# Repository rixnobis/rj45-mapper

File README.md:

# rj45-mapper

A bench probe for unknown cables that have an 8P8C (RJ45) plug on one end and loose
wires on the other. Plug the cable into the jack and touch one loose wire to the
pad. The LED for the jack pin that wire lands on lights up. If two pins are shorted
together in the cable, two LEDs light.

## How it works

The pad sits at 5 V through 1k. Each jack pin drives one input of a ULN2803A, and
each ULN output sinks one red LED through 330R (about 7 mA). A wire grounded at its
far end draws 5 mA from the pad, so it is not a short. A finger across the pad and a
wire (around 1 Mohm) puts the input under 0.1 V, far below the two-VBE turn-on of the
ULN input, so only metal contact lights an LED. Power is USB-C at 5 V, with a
separate 5.1k on each CC pin.

## Parts

JLC assembles everything except the jack: `fab/rj45-mapper-bom.csv` and
`fab/rj45-mapper-cpl.csv`. The jack is any unshielded right-angle 8P8C on the TE
5555164 / Amphenol 54602 land pattern (8 x 0.89 mm on 1.27 mm pitch, rows 2.54 mm
apart, 3.25 mm pegs 11.43 mm apart), bought separately and hand-soldered; see
`fab/hand-solder.csv`. Its plug face sits flush with the board edge. The 3D model
is TE 5555164-1. Check the part rotations in JLC's placement preview before
ordering (U1 and the LEDs are polarized).

## Case

`case/case.scad` (OpenSCAD) has a base and a lid that clamp the board between them
with four M3x18 screws through the mounting holes. The pilot holes in the base are
2.6 mm for self-tapping screws; set `PILOT_D = 4.0` for heat-set inserts. The lid has
one light tube per LED, with the channel numbers debossed beside them, and openings
for the jack, the USB-C plug and the pad. There are no overhangs that need support.
`case/fit_check.py` tests every component triangle of the populated board against
the case solids (the board meshes are not closed, so OpenSCAD cannot intersect them),
and casts rays along the plug path from outside the case to check that a plug can
reach 3 mm into the jack.

## Building

`tools/build.sh` regenerates everything: schematic, ERC, a pin-by-pin netlist check,
placement and a scripted route, pours, DRC with schematic parity, a routing geometry
check, renders and fab outputs. `case/render.sh` makes the case STLs and renders.
Needs KiCad 10 with `kicad-packages3d`, OpenSCAD and ImageMagick.

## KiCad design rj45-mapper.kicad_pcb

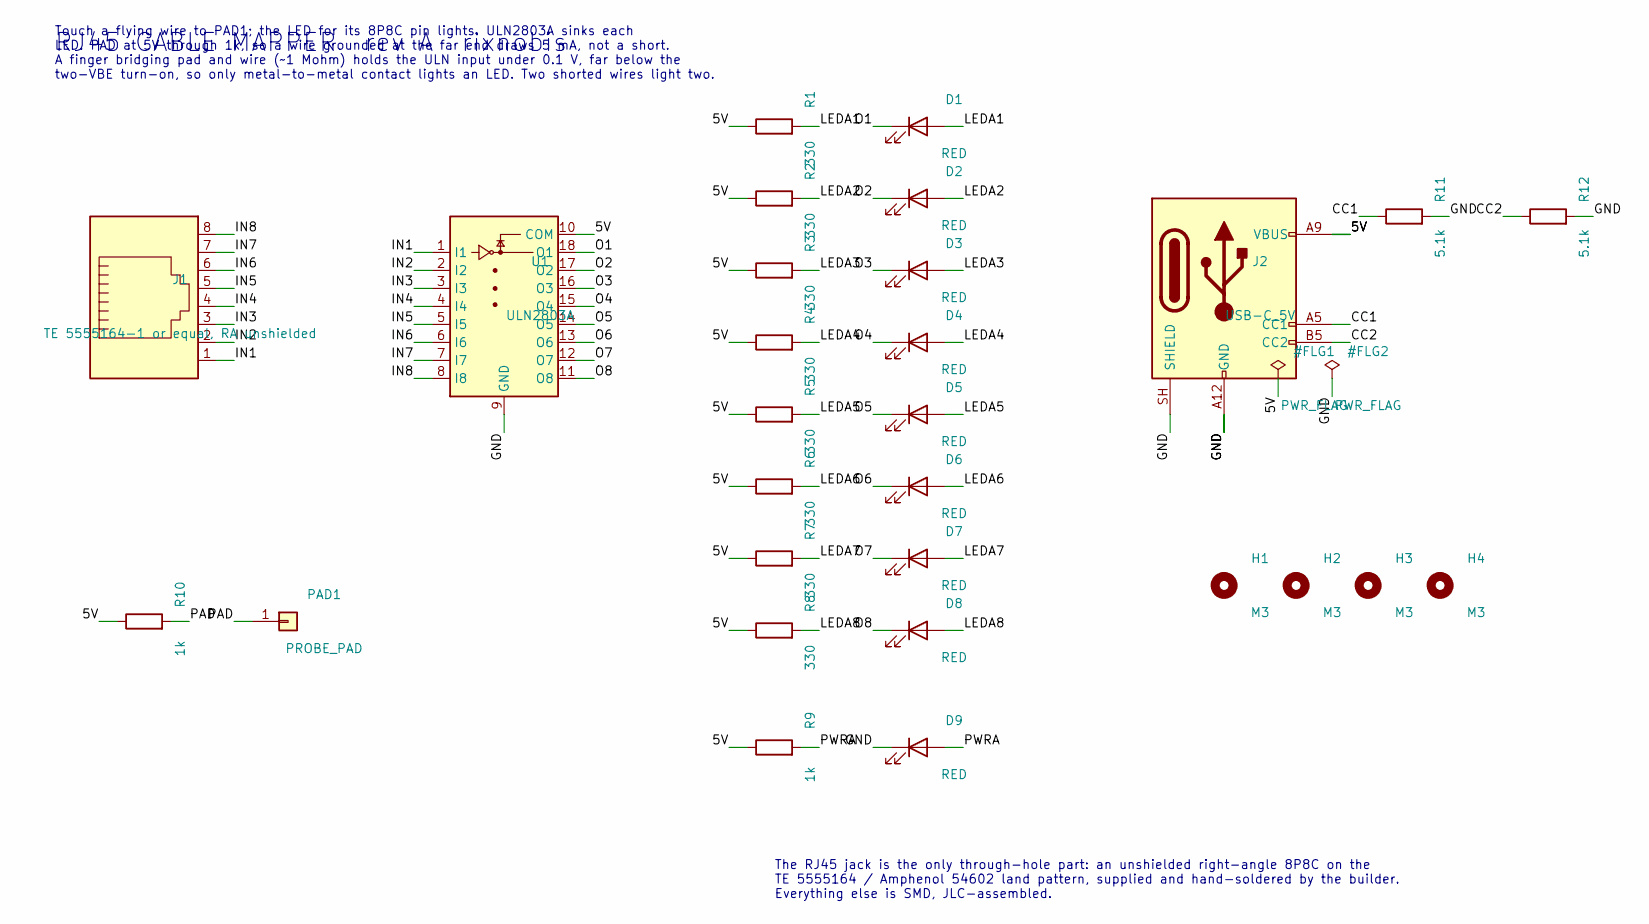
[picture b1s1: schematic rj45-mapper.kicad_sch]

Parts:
D1, D2, D3, D4, D5, D6, D7, D8, D9: RED; LED_1206_3216Metric; LCSC C84270
H1, H2, H3, H4: M3; MountingHole_3.2mm_M3
J1: TE 5555164-1 or equal, RA unshielded; RJ45_8P8C_RightAngle
J2: USB-C_5V; USB_C_Receptacle_GCT_USB4125-xx-x_6P_TopMnt_Horizontal; LCSC C3151650
PAD1: PROBE_PAD; ProbePad_15x15
R1, R2, R3, R4, R5, R6, R7, R8: 330; R_0805_2012Metric; LCSC C17630
R9, R10: 1k; R_0805_2012Metric; LCSC C17513
R11, R12: 5.1k; R_0805_2012Metric; LCSC C27834
U1: ULN2803A; SOIC-18W_7.5x11.6mm_P1.27mm; LCSC C845537

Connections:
/5V: J2.A9 (VBUS), J2.B9 (VBUS), R1.1, R2.1, R3.1, R4.1, R5.1, R6.1, R7.1, R8.1, R9.1, R10.1, U1.10 (COM)
/CC1: J2.A5 (CC1), R11.1
/CC2: J2.B5 (CC2), R12.1
/GND: D9.1 (K), J2.A12 (GND), J2.B12 (GND), J2.SH (SHIELD), R11.2, R12.2, U1.9 (GND)
/IN1: J1.1, U1.1 (I1)
/IN2: J1.2, U1.2 (I2)
/IN3: J1.3, U1.3 (I3)
/IN4: J1.4, U1.4 (I4)
/IN5: J1.5, U1.5 (I5)
/IN6: J1.6, U1.6 (I6)
/IN7: J1.7, U1.7 (I7)
/IN8: J1.8, U1.8 (I8)
/LEDA1: D1.2 (A), R1.2
/LEDA2: D2.2 (A), R2.2
/LEDA3: D3.2 (A), R3.2
/LEDA4: D4.2 (A), R4.2
/LEDA5: D5.2 (A), R5.2
/LEDA6: D6.2 (A), R6.2
/LEDA7: D7.2 (A), R7.2
/LEDA8: D8.2 (A), R8.2
/O1: D1.1 (K), U1.18 (O1)
/O2: D2.1 (K), U1.17 (O2)
/O3: D3.1 (K), U1.16 (O3)
/O4: D4.1 (K), U1.15 (O4)
/O5: D5.1 (K), U1.14 (O5)
/O6: D6.1 (K), U1.13 (O6)
/O7: D7.1 (K), U1.12 (O7)
/O8: D8.1 (K), U1.11 (O8)
/PAD: PAD1.1, R10.2
/PWRA: D9.2 (A), R9.2

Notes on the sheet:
RJ45 CABLE MAPPER rev A rixnobis
Touch a flying wire to PAD1; the LED for its 8P8C pin lights. ULN2803A sinks each LED. PAD at 5V through 1k, so a wire grounded at the far end draws 5 mA, not a short. A finger bridging pad and wire (~1 Mohm) holds the ULN input under 0.1 V, far below the two-VBE turn-on, so only metal-to-metal con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
The RJ45 jack is the only through-hole part: an unshielded right-angle 8P8C on the TE 5555164 / Amphenol 54602 land pattern, supplied and hand-soldered by the builder. Everything else is SMD, JLC-assembled.

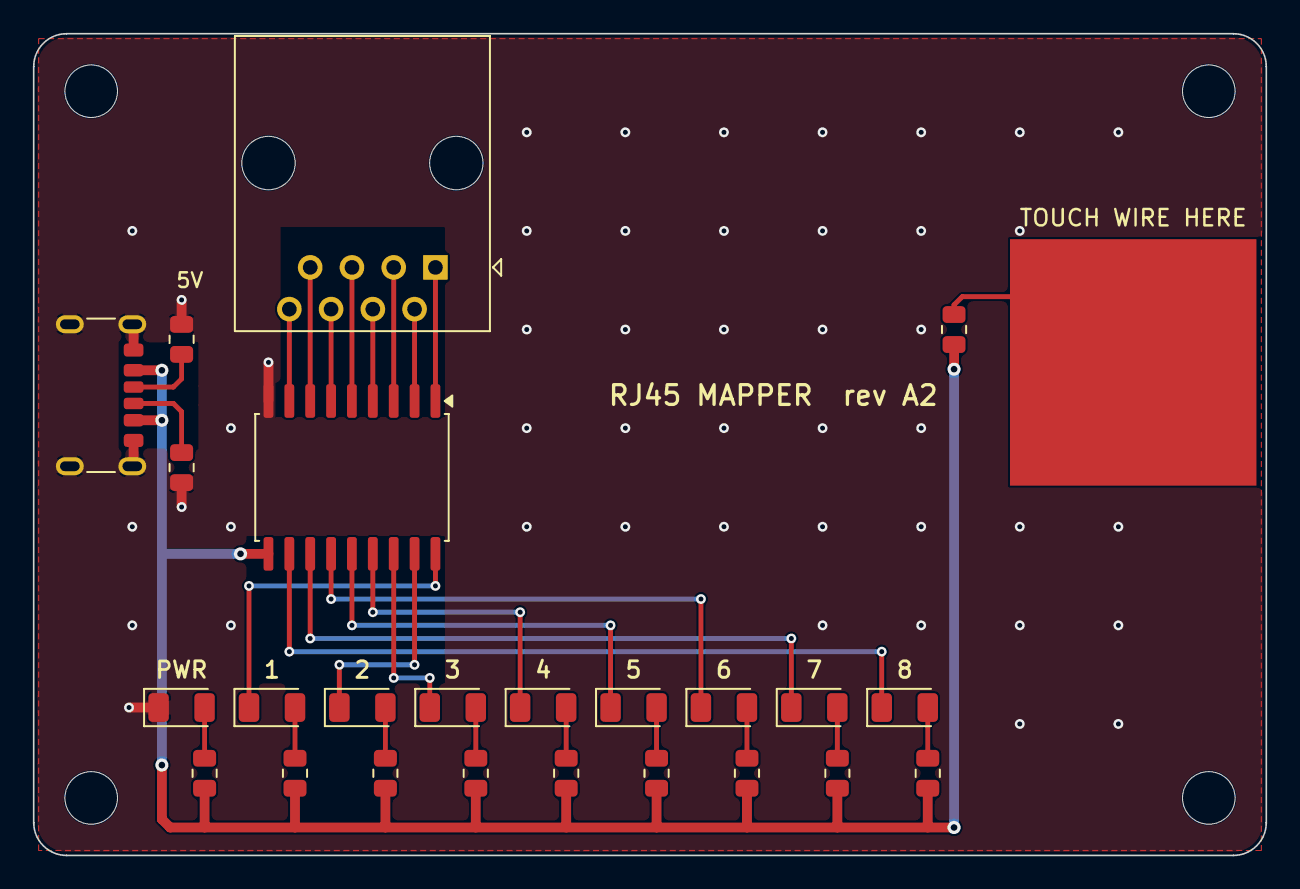
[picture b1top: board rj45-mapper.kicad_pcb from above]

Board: 2 copper layers, 75.0 x 50.0 mm, 29 parts (0 on the bottom side), 30 nets.

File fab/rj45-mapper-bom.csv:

"Comment","Designator","Footprint","LCSC Part #"
"RED","D1,D2,D3,D4,D5,D6,D7,D8,D9","LED_SMD:LED_1206_3216Metric","C84270"
"USB-C_5V","J2","Connector_USB:USB_C_Receptacle_GCT_USB4125-xx-x_6P_TopMnt_Horizontal","C3151650"
"330","R1,R2,R3,R4,R5,R6,R7,R8","Resistor_SMD:R_0805_2012Metric","C17630"
"1k","R9,R10","Resistor_SMD:R_0805_2012Metric","C17513"
"5.1k","R11,R12","Resistor_SMD:R_0805_2012Metric","C27834"
"ULN2803A","U1","Package_SO:SOIC-18W_7.5x11.6mm_P1.27mm","C845537"
